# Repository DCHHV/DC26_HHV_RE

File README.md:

# DC26 HHV RE Challenge
DEF CON 26 Hardware Hacking Village Reverse Engineering Challenge

## Overview

This year's board features two challenge. The first part requires entering in the correct passcode using the four onboard buttons (labeled A, B, C, and D). Once the correct passcode has been entered, the middle, green LED will come on and the flag will be printed out via the serial interface. The second part of the challenge requires understanding how the second IC (the first being the ATtiny microcontroller) is used and manipulating that. The bottom, green LED will come on once that part is solved.

There are multiple ways to solve these challenges, and they are meant to be fun. If you're having trouble, or if you find a bug, reach out to [mediumrehr](https://www.twitter.com/mediumrehr)

Good luck!

## Instuctions

### Assembly
If your challenge isn't assembled, please see the hardware section for details on assembly. Most parts are explanitory as to where they go. For the surface mount parts, the 3-pack of resistors are for the LEDs, the 2-pack of resistors is for the RX line (only one of the resistors are necessary), and the single capacitor is used to reduce noise on the VCC input.

### Programming
There are two methods of loading the firmware onto the challenge board. Both require the same steps to start.

1. Connect the test points on the bottom of the challenge board to an arduino and add a capacitor between reset and GND on the Arduino UNO.

```
GND --> GND
SCK --> pin 13
MISO -> pin 12
MOSI -> pin 11
CS ---> pin 10
VCC --> 5V
```

Note 1: If using an Uno (or another arduino board with 5V IO pins), make sure VCC is connected to 5V when programming. If IO pins are 3.3V, connect VCC to 3.3V when programming.

2. Bridge the two pads to the bottom right of the buttons.

3. Install the [Arduino IDE](https://www.arduino.cc/en/Main/Software "Arduino IDE Download").

4. Configure the Arduino as an ISP and add support to the Arduino IDE for the Attiny84 by [following this guide](http://highlowtech.org/?p=1695 "Guide for adding ATtiny84 support in Arduino IDE").

Now, here's where things split. You can either use the Arduino IDE to compile and upload the firmware onto the board, or you can use avrdude to program the already compiled code onto the board. The former requires installing a couple Arduino IDE libraries.

**Using the Arduino IDE**

1. Install the [TinyWireM](https://github.com/adafruit/TinyWireM) library by cloning/downloading and unzipping the project into `Arduino/libraries`, likely in your Documents folder.

2. Connect the Arduino to the computer and under the `Tools` menu, set `Board` to `ATtiny24/44/84`, `Processor` to `ATtiny84`, `Clock` to `Internal 1 MHz`, `Port` should be whatever port the Arduino UNO is plugged into, and `Programmer` to `Arduino as ISP`.

3. Burn the bootloader (and set the clock speed) by going back to `Tools` and clicking `Burn Bootloader`

4. Once the bootloader is burned onto the Attiny84, open `DC26_HHV_RE_setup.ino` and click the right-pointing arrow in the top left corner to upload the sketch. This will configure the challenges board before loading the challenge. The red LED should come on once this step is finished (if the LED hasn't come on after a couple seconds, it's likely something went wrong).

5. Open and upload `DC26_HHV_RE_obfuscated.ino` (DC26_HHV_RE.ino does the same thing, it's just easier to read and might give away some of the fun of the game if you read the wrong line or two) to finish loading the challenge.

Ensure that the red LED appears briefly upon pressing one of the buttons. If it does, you're good to go! Disconnect the programming wires and Arduino power before putting a battery into the battery holder.

6. Remove the solder bridge on the two pads to the bottom right of the buttons.

**Using avrdude**

avrdude has the benefit of allowing you to flash the hex file, and therefor not needing to install another library, or possibly spoil the surprises of the challenge.

1. Make sure you you know the location of avrdude and its config file, your programmer id, and the path to the mounted usb device. The config file will come after `-C`, the programmer id after `-c`, and the programmer mount location after `-P`.

In Mac OS, the avrdude will likely be under `/Applications/Arduino.app/Contents/Java/hardware/tools/avr/bin/avrdude` and its config will likely be under `/Applications/Arduino.app/Contents/Java/hardware/tools/avr/etc/avrdude.conf`. If you're using Windows, avrdude will likely be under `C:\Program Files (x86)\Arduino\hardware\tools\avr\bin\avrdude` and its config will likely be under `C:\Program Files (x86)\Arduino\hardware\tools\avr\etc\avrdude.conf`.

If you're using an Arduino as ISP, the programmer id is likely `stk500v1`, if you're using a bus pirate, the id is likely `buspirate`. For more examples of programmer ids, see [Ladyada's Avrdude Tutorial](http://www.ladyada.net/learn/avr/avrdude.html).

To find the programmer's port, follow [this guide](https://www.mathworks.com/help/supportpkg/arduinoio/ug/find-arduino-port-on-windows-mac-and-linux.html), or something similar.

2. Burn the bootloader. This script will setup the attiny84 bootloader and configure it to use the 1MHz internal clock:
```
/path/to/avrdude -C /path/to/avrdude.conf -v -p attiny84 -c stk500v1 -P /path/to/usbport -b 19200 -e -U efuse:w:0xff:m -U hfuse:w:0xdf:m -U lfuse:w:0x62:m
```

3. Load and run the setup sketch:
```
/path/to/avrdude -C /path/to/avrdude.conf -v -V -p attiny84 -c stk500v1 -P /path/to/usbport -b 19200 -U flash:w:/path/to/DC26_HHV_RE_setup.1MHz.hex:i
```

This will configure the challenges board before loading the challenge. The red LED should come on once this step is finished (if the LED hasn't come on after a couple seconds, it's likely something went wrong).

4. Load and run the challenge sketch:
```
/path/to/avrdude -C /path/to/avrdude.conf -v -V -p attiny84 -c stk500v1 -P /path/to/usbport -b 19200 -U flash:w:/path/to/DC26_HHV_RE.1MHz.hex:i
```

Ensure that the red LED appears briefly upon pressing one of the buttons. If it does, you're good to go! Disconnect the programming wires and Arduino power before putting a battery into the battery holder.

6. Remove the solder bridge on the two pads to the bottom right of the buttons.

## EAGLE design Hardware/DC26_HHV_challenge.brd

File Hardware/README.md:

# DC26 HHV RE Challenge
DEF CON 26 Hardware Hacking Village Reverse Engineering Challenge

## Assembly

The schematic, layout, and BOM are all included in this folder. Before assembling, make sure you have correct parts, and the correct amount of each.

```
SMD parts:
3 75 Ohm 0603 resistors
1* 1k Ohm 0805 resistor
1 0.1uF 0603 capacitor

TH parts:
1 ATtiny84 IC
1 24LC256 IC
4 Tactile switches 6mm
7 10k Ohm resistors
2 Green LEDs 5mm
1 Red LED 5mm
1 CR2032 battery holder
1 CR2032 battery

Not included, but likely necessary:
a handful of male headers
a serial reader
some connection wire

* if you received parts at DEF CON, you likely received this as a pack of 2, but you'll only need one
```

Below is what the assembled challenge board should look like:

Most of the through hole components can only go once place. The ATtiny and 24LC256 are directional, so make sure they oriented correctly (notches should line up with silkscreened indicators). The LEDs should be in the order of red (or clear), green, green from the top down. Surface mount componets are noted in the image above. The three 75 Ohm resistors should be placed directly above each LED, capacitor should be placed to the top left of the ATtiny84, and the 1k Ohm resistor should be placed on the RX serial line (above the ATtiny84).

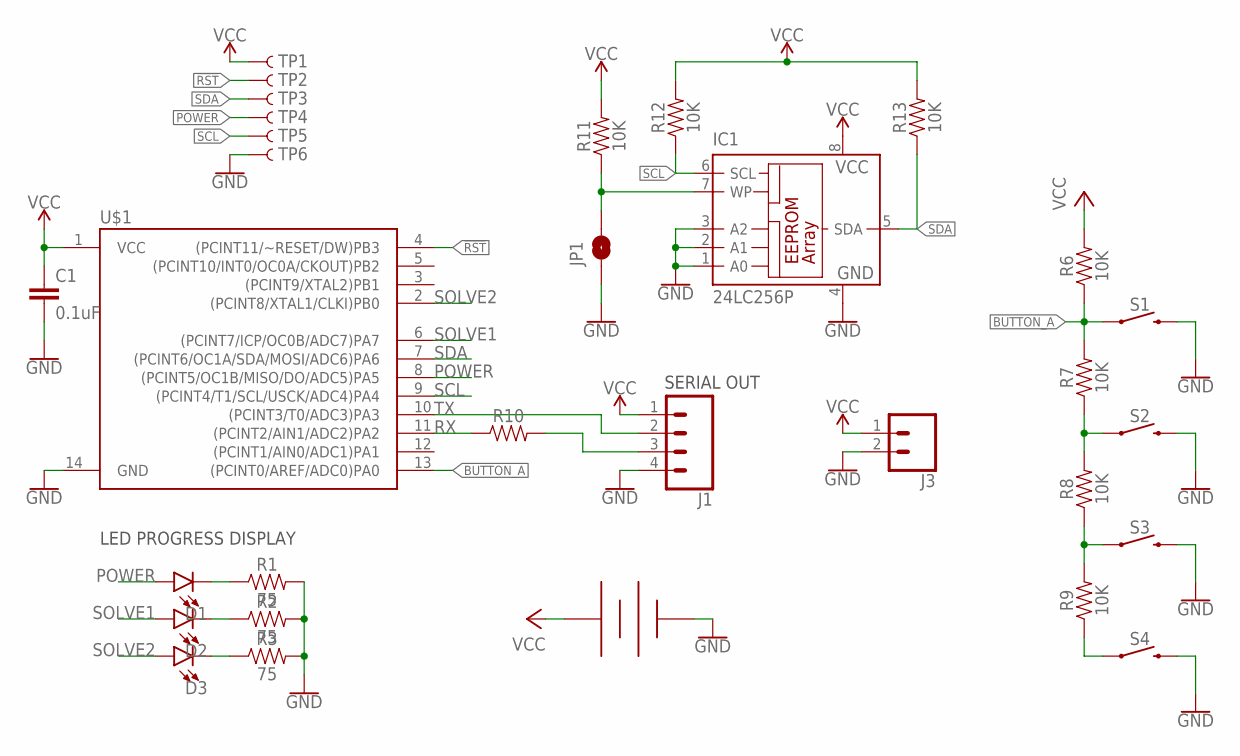
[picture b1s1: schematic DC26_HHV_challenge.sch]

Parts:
BT1: BAT-HLD-001-THM
C1: 0.1uF; 0603
D1, D2, D3: LED5MM; LED_5MM
IC1: 24LC256P; DIL8
J1: CONN_04LOCK; 1X04_LOCK
J3: CONN_02PTH3; 1X02_LONGPADS
JP1: JUMPER-SMT_2_NO_SILK; SMT-JUMPER_2_NO_SILK
R1, R2, R3: 75; 0805
R6, R7, R8, R9, R11, R12, R13: 10K; AXIAL-0.3
R10: 0805
S1, S2, S3, S4: MOMENTARY-SWITCH-SPST-PTH-6.0MM; TACTILE_SWITCH_PTH_6.0MM
TP1, TP2, TP3, TP4, TP5, TP6: TEST-POINT3X4; PAD.03X.04
U$1: ATTINY84ATTINY84-20PU; DIP14

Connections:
!RST: TP2.P$1, U$1.4 ((PCINT11/~RESET/DW)PB3)
BUTTON_A: R6.P$1 (1), R7.P$2 (2), S1.1, U$1.13 ((PCINT0/AREF/ADC0)PA0)
GND: BT1.- (VSS), C1.2, IC1.1 (A0), IC1.2 (A1), IC1.3 (A2), IC1.4 (GND), J1.4, J3.2, JP1.1, R1.2, R2.2, R3.2, S1.3 (2), S2.3 (2), S3.3 (2), S4.3 (2), TP6.P$1, U$1.14 (GND)
unnamed: R9.P$1 (1), S4.1
unnamed: R8.P$1 (1), R9.P$2 (2), S3.1
unnamed: R7.P$1 (1), R8.P$2 (2), S2.1
unnamed: D1.K (C), R1.1
unnamed: D2.K (C), R2.1
unnamed: D3.K (C), R3.1
unnamed: R10.1, U$1.11 ((PCINT2/AIN1/ADC2)PA2)
unnamed: IC1.7 (WP), JP1.2, R11.P$1 (1)
POWER: D1.A, TP4.P$1, U$1.8 ((PCINT5/OC1B/MISO/DO/ADC5)PA5)
RX: J1.3, R10.2
SCL: IC1.6 (SCL), R12.P$1 (1), TP5.P$1, U$1.9 ((PCINT4/T1/SCL/USCK/ADC4)PA4)
SDA: IC1.5 (SDA), R13.P$1 (1), TP3.P$1, U$1.7 ((PCINT6/OC1A/SDA/MOSI/ADC6)PA6)
SOLVE1: D2.A, U$1.6 ((PCINT7/ICP/OC0B/ADC7)PA7)
SOLVE2: D3.A, U$1.2 ((PCINT8/XTAL1/CLKI)PB0)
TX: J1.2, U$1.10 ((PCINT3/T0/ADC3)PA3)
VCC: BT1.+@0 (VCC), BT1.+@1 (VCC), BT1.+@2 (VCC), BT1.+@3 (VCC), C1.1, IC1.8 (VCC), J1.1, J3.1, R6.P$2 (2), R11.P$2 (2), R12.P$2 (2), R13.P$2 (2), TP1.P$1, U$1.1 (VCC)

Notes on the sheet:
SERIAL OUT
LED PROGRESS DISPLAY

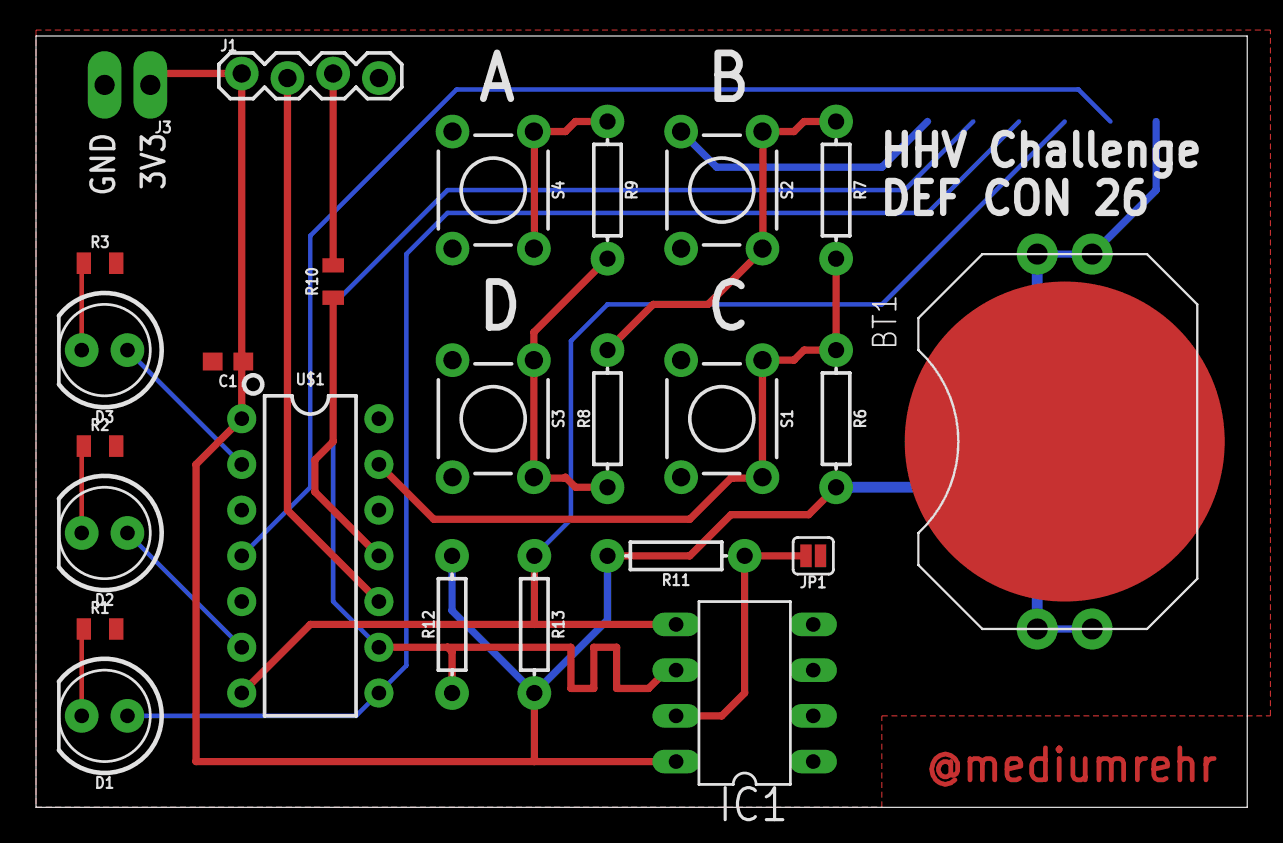
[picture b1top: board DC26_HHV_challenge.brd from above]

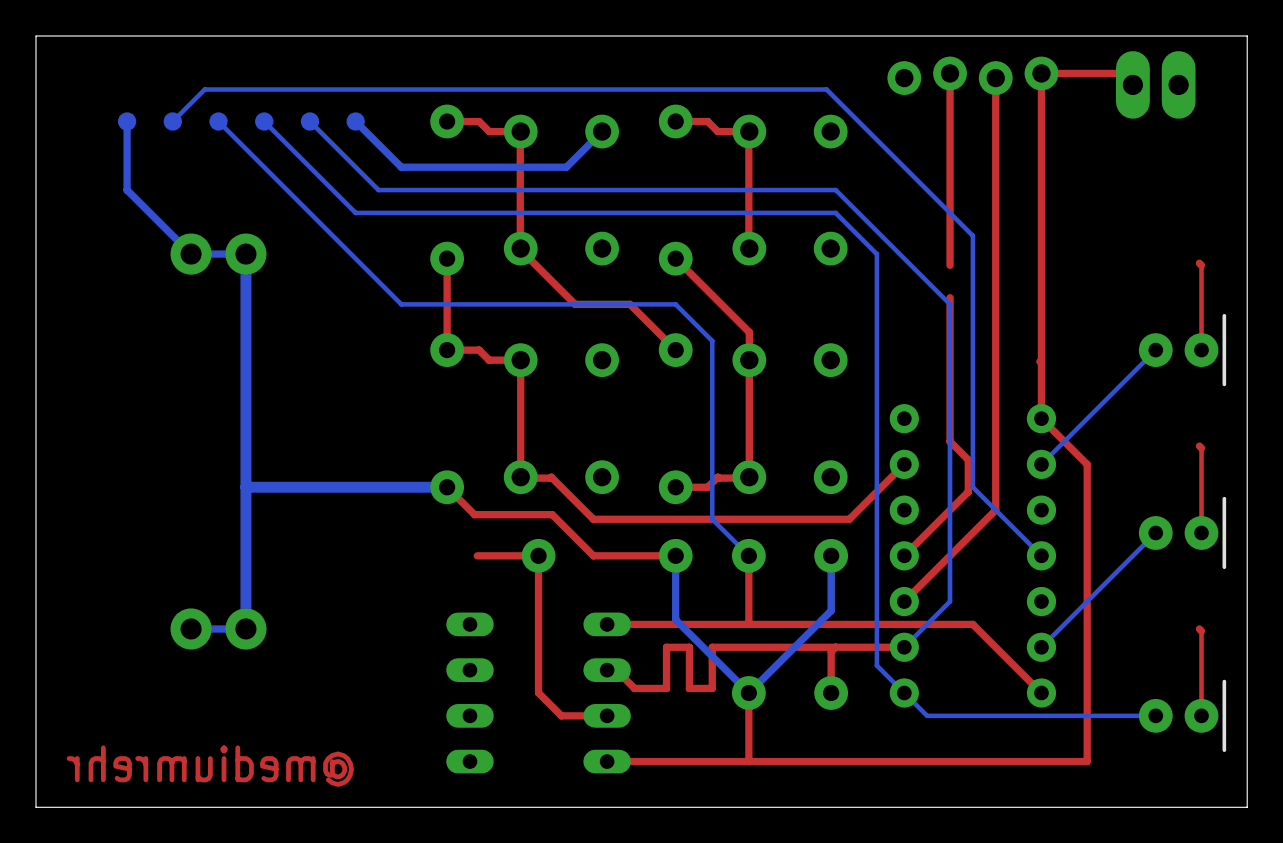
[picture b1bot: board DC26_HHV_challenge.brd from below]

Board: 2 copper layers, 67.3 x 42.9 mm, 31 parts (6 on the bottom side), 19 nets.

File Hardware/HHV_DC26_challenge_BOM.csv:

DC26 HHV RE Challenge BOM,,,,,,,,,,,
,,,,,,,,,,,
Part,Value,Device,Package,Description,MF,MPN,Digikey PN,Digikey link,,,
BT1,,Batter Holder,,RETAINER BATT CR2025/2032 PC PIN,Linx Technologies Inc,BAT-HLD-001-THM,BAT-HLD-001-THM-ND,https://www.digikey.com/product-detail/en/linx-technologies-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,,,
C1,0.1uF,Capacitor,603,CAP CER 0.1UF 25V X5R 0603,Samsung Electro-Mechanics,CL10A104KA8NNNC,1276-1857-1-ND,https://www.digikey.com/product-detail/en/samsung-electro-me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,,,
D1,Green,LED5MM,LED_5MM,LED GREEN DIFFUSED 5MM ROUND T/H,Marktech Optoelectronics,MT2118-G-A,1125-1184-ND,https://www.digikey.com/product-detail/en/marktech-optoelect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,,,
D2,Green,LED5MM,LED_5MM,LED GREEN DIFFUSED 5MM ROUND T/H,,,,,,,
D3,Red,LED5MM,LED_5MM,LED RED CLEAR 5MM ROUND T/H,Cree Inc.,C503B-RAN-CZ0C0AA2,C503B-RAN-CZ0C0AA2CT-ND,https://www.digikey.com/product-detail/en/cree-inc/C503B-RAN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,,,
IC1,,24LC256P,DIL8,IC EEPROM 256K I2C 400KHZ 8DIP,Microchip Technologies,24LC256-I/P,24LC256-I/P-ND,https://www.digikey.com/product-detail/en/microchip-technolo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,,,
R1,75,Resistor,805,RES SMD 75 OHM 5% 1/10W 0603,Vishay Dale,CRCW060375R0JNEA,541-75GCT-ND,https://www.digikey.com/product-detail/en/vishay-dale/CRCW06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,,,
R2,75,Resistor,805,RES SMD 75 OHM 5% 1/10W 0603,,,,,,,
R3,75,Resistor,805,RES SMD 75 OHM 5% 1/10W 0603,,,,,,,
R10,1k,Resistor,805,RES SMD 1K OHM 5% 1/8W 0805,Vishay Dale,CRCW08051K00JNEAC,541-4162-1-ND,https://www.digikey.com/product-detail/en/vishay-dale/CRCW08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,,,
R6,10K,Resistor,AXIAL-0.3,RES 10K OHM 1/4W 5% AXIAL,Stackpole Electronics Inc.,CF14JT10K0,CF14JT10K0CT-ND,https://www.digikey.com/product-detail/en/stackpole-electron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,,,
R7,10K,Resistor,AXIAL-0.3,RES 10K OHM 1/4W 5% AXIAL,,,,,,,
R8,10K,Resistor,AXIAL-0.3,RES 10K OHM 1/4W 5% AXIAL,,,,,,,
R9,10K,Resistor,AXIAL-0.3,RES 10K OHM 1/4W 5% AXIAL,,,,,,,
R11,10K,Resistor,AXIAL-0.3,RES 10K OHM 1/4W 5% AXIAL,,,,,,,
R12,10K,Resistor,AXIAL-0.3,RES 10K OHM 1/4W 5% AXIAL,,,,,,,
R13,10K,Resistor,AXIAL-0.3,RES 10K OHM 1/4W 5% AXIAL,,,,, ,, 
S1,,SPST Momentary Switch,TACTILE_SWITCH_PTH_6.0MM,SWITCH TACTILE SPST-NO 0.05A 12V,APEM Inc,MJTP1230,679-2428-ND,https://www.digikey.com/product-detail/en/apem-inc/MJTP1230/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,,,
S2,,SPST Momentary Switch,TACTILE_SWITCH_PTH_6.0MM,SWITCH TACTILE SPST-NO 0.05A 12V,,,,,,,
S3,,SPST Momentary Switch,TACTILE_SWITCH_PTH_6.0MM,SWITCH TACTILE SPST-NO 0.05A 12V,,,,,,,
S4,,SPST Momentary Switch,TACTILE_SWITCH_PTH_6.0MM,SWITCH TACTILE SPST-NO 0.05A 12V,,,,,,,
U$1,,ATTINY84-20PU,DIP14,IC MCU 8BIT 8KB FLASH 14DIP,Microchip Technologies,ATTINY84A-PU,ATTINY84A-PU-ND,https://www.digikey.com/product-detail/en/microchip-technolo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,,,
,,,,,,,,,,,
Battery,,,"Coin, 20mm",BATTERY LITHIUM 3V COIN 20MM,Panasonic - BSG,CR2032,P189-ND,https://www.digikey.com/product-detail/en/panasonic-bsg/CR20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,,,

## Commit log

2018-08-29 add avrdude instructions and hex files
2018-09-20 add solution write-up

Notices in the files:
parts and their libraries:
SparkFun-Capacitors: Licensing: Creative Commons ShareAlike 4.0 International - https://creativecommons.org/licenses/by-sa/4.0
